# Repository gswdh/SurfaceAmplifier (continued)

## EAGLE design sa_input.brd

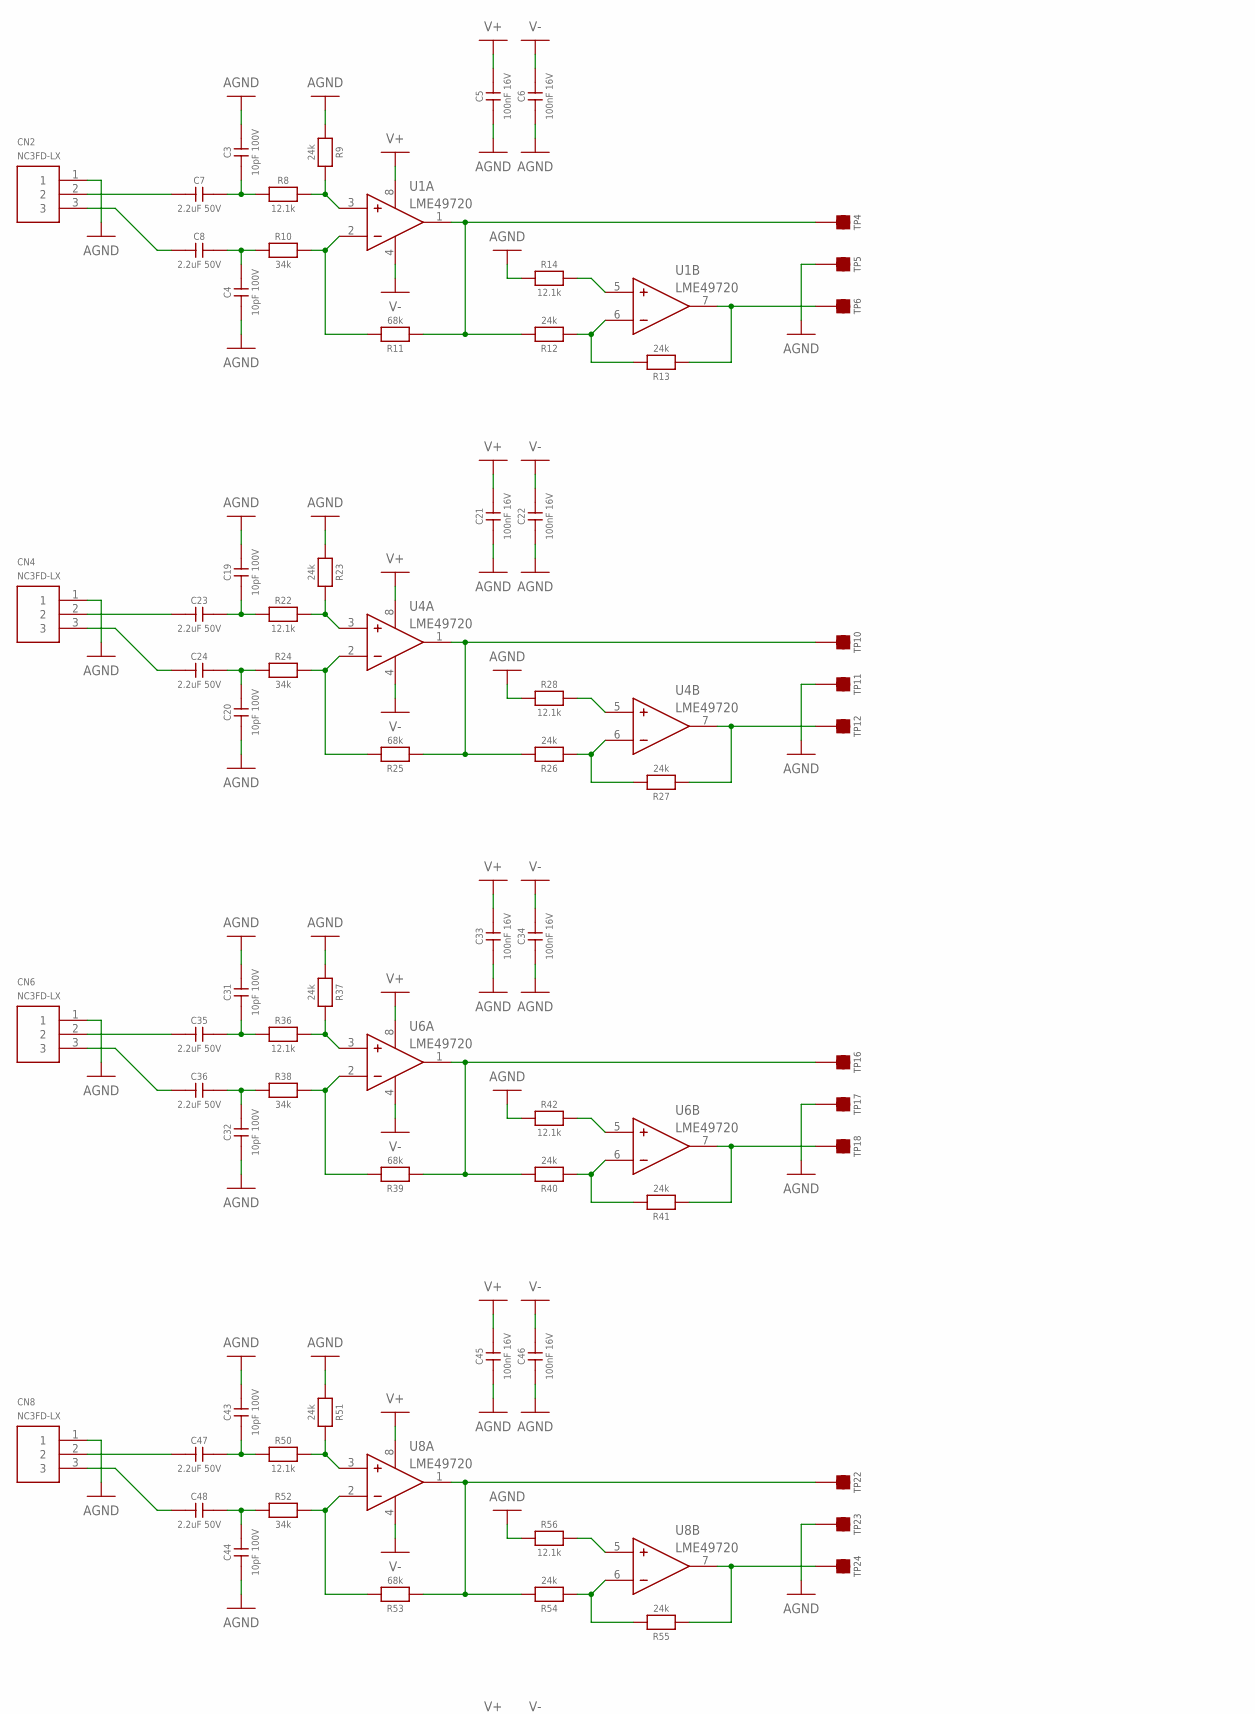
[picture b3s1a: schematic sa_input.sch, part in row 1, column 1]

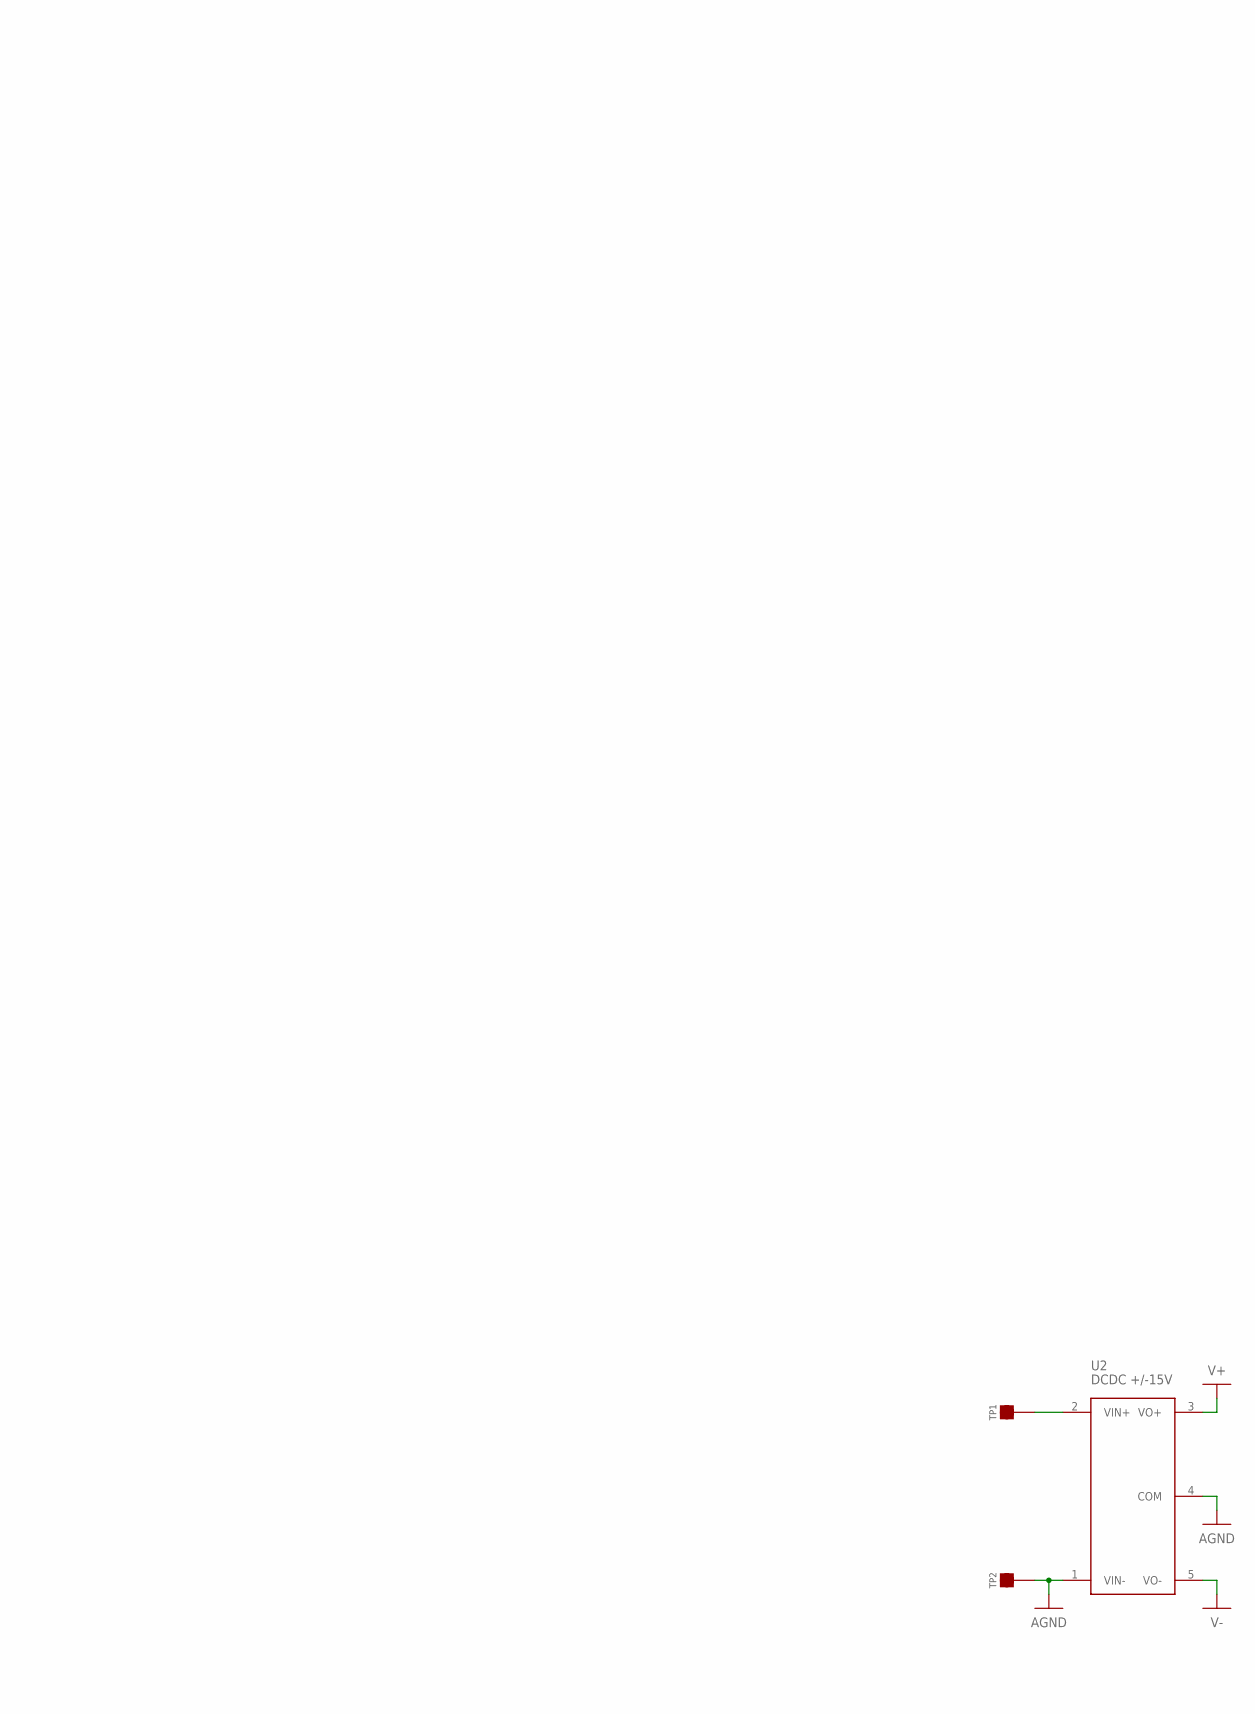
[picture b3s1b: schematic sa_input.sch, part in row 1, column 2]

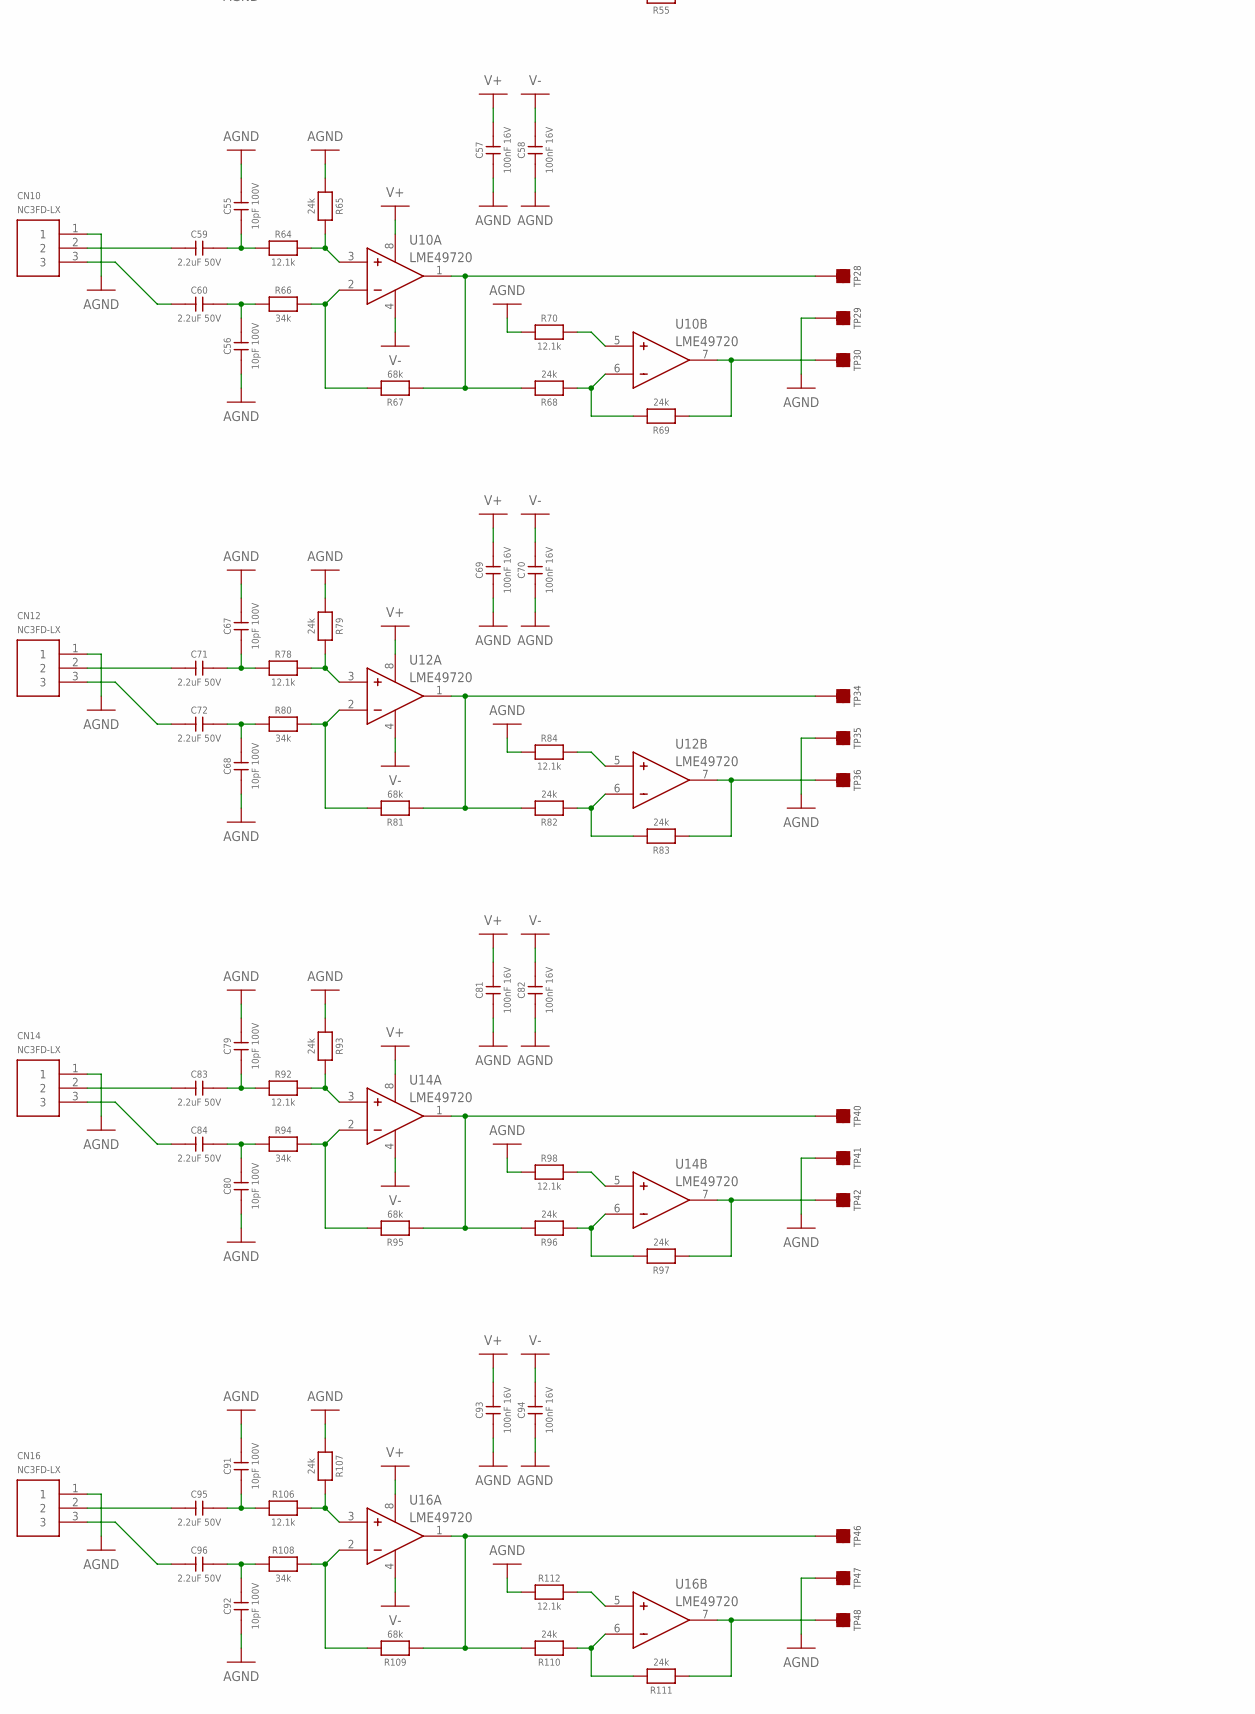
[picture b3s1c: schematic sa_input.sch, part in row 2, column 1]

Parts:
C3, C4, C19, C20, C31, C32, C43, C44, C55, C56, C67, C68, C79, C80, C91, C92: 10pF 100V; 0603
C5, C6, C21, C22, C33, C34, C45, C46, C57, C58, C69, C70, C81, C82, C93, C94: 100nF 16V; 0603
C7, C8, C23, C24, C35, C36, C47, C48, C59, C60, C71, C72, C83, C84, C95, C96: 2.2uF 50V; 5X7.2BOX
CN2, CN4, CN6, CN8, CN10, CN12, CN14, CN16: NC3FD-LX
R8, R14, R22, R28, R36, R42, R50, R56, R64, R70, R78, R84, R92, R98, R106, R112: 12.1k; 0603
R9, R12, R13, R23, R26, R27, R37, R40, R41, R51, R54, R55, R65, R68, R69, R79, R82, R83, R93, R96, R97, R107, R110, R111: 24k; 0603
R10, R24, R38, R52, R66, R80, R94, R108: 34k; 0603
R11, R25, R39, R53, R67, R81, R95, R109: 68k; 0603
TP1, TP2, TP4, TP5, TP6, TP10, TP11, TP12, TP16, TP17, TP18, TP22, TP23, TP24, TP28, TP29, TP30, TP34, TP35, TP36, TP40, TP41, TP42, TP46, TP47, TP48: TEST_POINT_SQUARE; OSPREY_HSS_PAD
U1, U4, U6, U8, U10, U12, U14, U16: LME49720; SO8
U2: DCDC +/-15V; PDQE10

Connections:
AGND: C3.1, C4.1, C5.1, C6.1, C19.1, C20.1, C21.1, C22.1, C31.1, C32.1, C33.1, C34.1, C43.1, C44.1, C45.1, C46.1, C55.1, C56.1, C57.1, C58.1, C67.1, C68.1, C69.1, C70.1, C79.1, C80.1, C81.1, C82.1, C91.1, C92.1, C93.1, C94.1, CN2.1, CN4.1, CN6.1, CN8.1, CN10.1, CN12.1, CN14.1, CN16.1, R9.1, R14.1, R23.1, R28.1, R37.1, R42.1, R51.1, R56.1, R65.1, R70.1, R79.1, R84.1, R93.1, R98.1, R107.1, R112.1, TP2.1, TP5.1, TP11.1, TP17.1, TP23.1, TP29.1, TP35.1, TP41.1, TP47.1, U2.1 (VIN-), U2.4 (COM)
unnamed: TP1.1, U2.2 (VIN+)
unnamed: R8.2, R9.2, U1.3 (+)
unnamed: R10.2, R11.2, U1.2 (-)
unnamed: C3.2, C7.2, R8.1
unnamed: C4.2, C8.2, R10.1
unnamed: C7.1, CN2.2
unnamed: C8.1, CN2.3
unnamed: R12.1, R13.2, U1.6 (-)
unnamed: R14.2, U1.5 (+)
unnamed: R22.2, R23.2, U4.3 (+)
unnamed: R24.2, R25.2, U4.2 (-)
unnamed: C19.2, C23.2, R22.1
unnamed: C20.2, C24.2, R24.1
unnamed: C23.1, CN4.2
unnamed: C24.1, CN4.3
unnamed: R26.1, R27.2, U4.6 (-)
unnamed: R28.2, U4.5 (+)
unnamed: R36.2, R37.2, U6.3 (+)
unnamed: R38.2, R39.2, U6.2 (-)
unnamed: C31.2, C35.2, R36.1
unnamed: C32.2, C36.2, R38.1
unnamed: C35.1, CN6.2
unnamed: C36.1, CN6.3
unnamed: R40.1, R41.2, U6.6 (-)
unnamed: R42.2, U6.5 (+)
unnamed: R50.2, R51.2, U8.3 (+)
unnamed: R52.2, R53.2, U8.2 (-)
unnamed: C43.2, C47.2, R50.1
unnamed: C44.2, C48.2, R52.1
unnamed: C47.1, CN8.2
unnamed: C48.1, CN8.3
unnamed: R54.1, R55.2, U8.6 (-)
unnamed: R56.2, U8.5 (+)
unnamed: R64.2, R65.2, U10.3 (+)
unnamed: R66.2, R67.2, U10.2 (-)
unnamed: C55.2, C59.2, R64.1
unnamed: C56.2, C60.2, R66.1
unnamed: C59.1, CN10.2
unnamed: C60.1, CN10.3
unnamed: R68.1, R69.2, U10.6 (-)
unnamed: R70.2, U10.5 (+)
unnamed: R78.2, R79.2, U12.3 (+)
unnamed: R80.2, R81.2, U12.2 (-)
unnamed: C67.2, C71.2, R78.1
unnamed: C68.2, C72.2, R80.1
unnamed: C71.1, CN12.2
unnamed: C72.1, CN12.3
unnamed: R82.1, R83.2, U12.6 (-)
unnamed: R84.2, U12.5 (+)
unnamed: R92.2, R93.2, U14.3 (+)
unnamed: R94.2, R95.2, U14.2 (-)
unnamed: C79.2, C83.2, R92.1
unnamed: C80.2, C84.2, R94.1
unnamed: C83.1, CN14.2
unnamed: C84.1, CN14.3
unnamed: R96.1, R97.2, U14.6 (-)
unnamed: R98.2, U14.5 (+)
unnamed: R106.2, R107.2, U16.3 (+)
unnamed: R108.2, R109.2, U16.2 (-)
unnamed: C91.2, C95.2, R106.1
unnamed: C92.2, C96.2, R108.1
unnamed: C95.1, CN16.2
unnamed: C96.1, CN16.3
unnamed: R110.1, R111.2, U16.6 (-)
unnamed: R112.2, U16.5 (+)
V+: C5.2, C21.2, C33.2, C45.2, C57.2, C69.2, C81.2, C93.2, U1.8 (V+), U2.3 (VO+), U4.8 (V+), U6.8 (V+), U8.8 (V+), U10.8 (V+), U12.8 (V+), U14.8 (V+), U16.8 (V+)
V-: C6.2, C22.2, C34.2, C46.2, C58.2, C70.2, C82.2, C94.2, U1.4 (V-), U2.5 (VO-), U4.4 (V-), U6.4 (V-), U8.4 (V-), U10.4 (V-), U12.4 (V-), U14.4 (V-), U16.4 (V-)
VOUT_N_1: R13.1, TP6.1, U1.7 (OUT)
VOUT_N_3: R27.1, TP12.1, U4.7 (OUT)
VOUT_N_5: R41.1, TP18.1, U6.7 (OUT)
VOUT_N_7: R55.1, TP24.1, U8.7 (OUT)
VOUT_N_9: R69.1, TP30.1, U10.7 (OUT)
VOUT_N_11: R83.1, TP36.1, U12.7 (OUT)
VOUT_N_13: R97.1, TP42.1, U14.7 (OUT)
VOUT_N_15: R111.1, TP48.1, U16.7 (OUT)
VOUT_P_1: R11.1, R12.2, TP4.1, U1.1 (OUT)
VOUT_P_3: R25.1, R26.2, TP10.1, U4.1 (OUT)
VOUT_P_5: R39.1, R40.2, TP16.1, U6.1 (OUT)
VOUT_P_7: R53.1, R54.2, TP22.1, U8.1 (OUT)
VOUT_P_9: R67.1, R68.2, TP28.1, U10.1 (OUT)
VOUT_P_11: R81.1, R82.2, TP34.1, U12.1 (OUT)
VOUT_P_13: R95.1, R96.2, TP40.1, U14.1 (OUT)
VOUT_P_15: R109.1, R110.2, TP46.1, U16.1 (OUT)

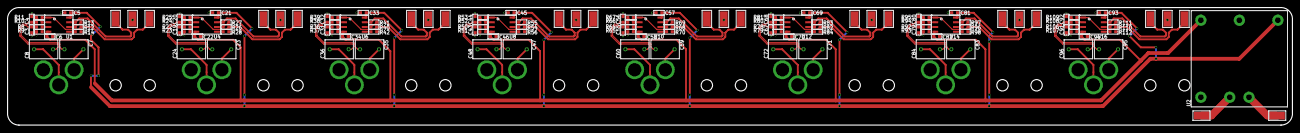
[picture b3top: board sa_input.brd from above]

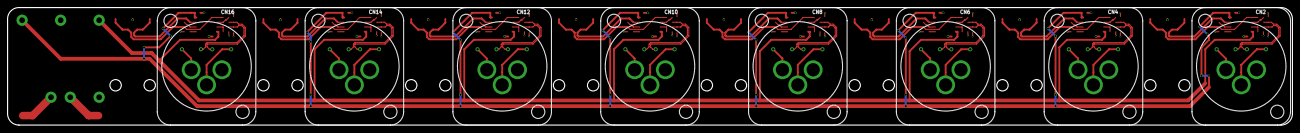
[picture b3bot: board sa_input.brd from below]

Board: 4 copper layers, 339.0 x 31.0 mm, 147 parts (8 on the bottom side), 84 nets.

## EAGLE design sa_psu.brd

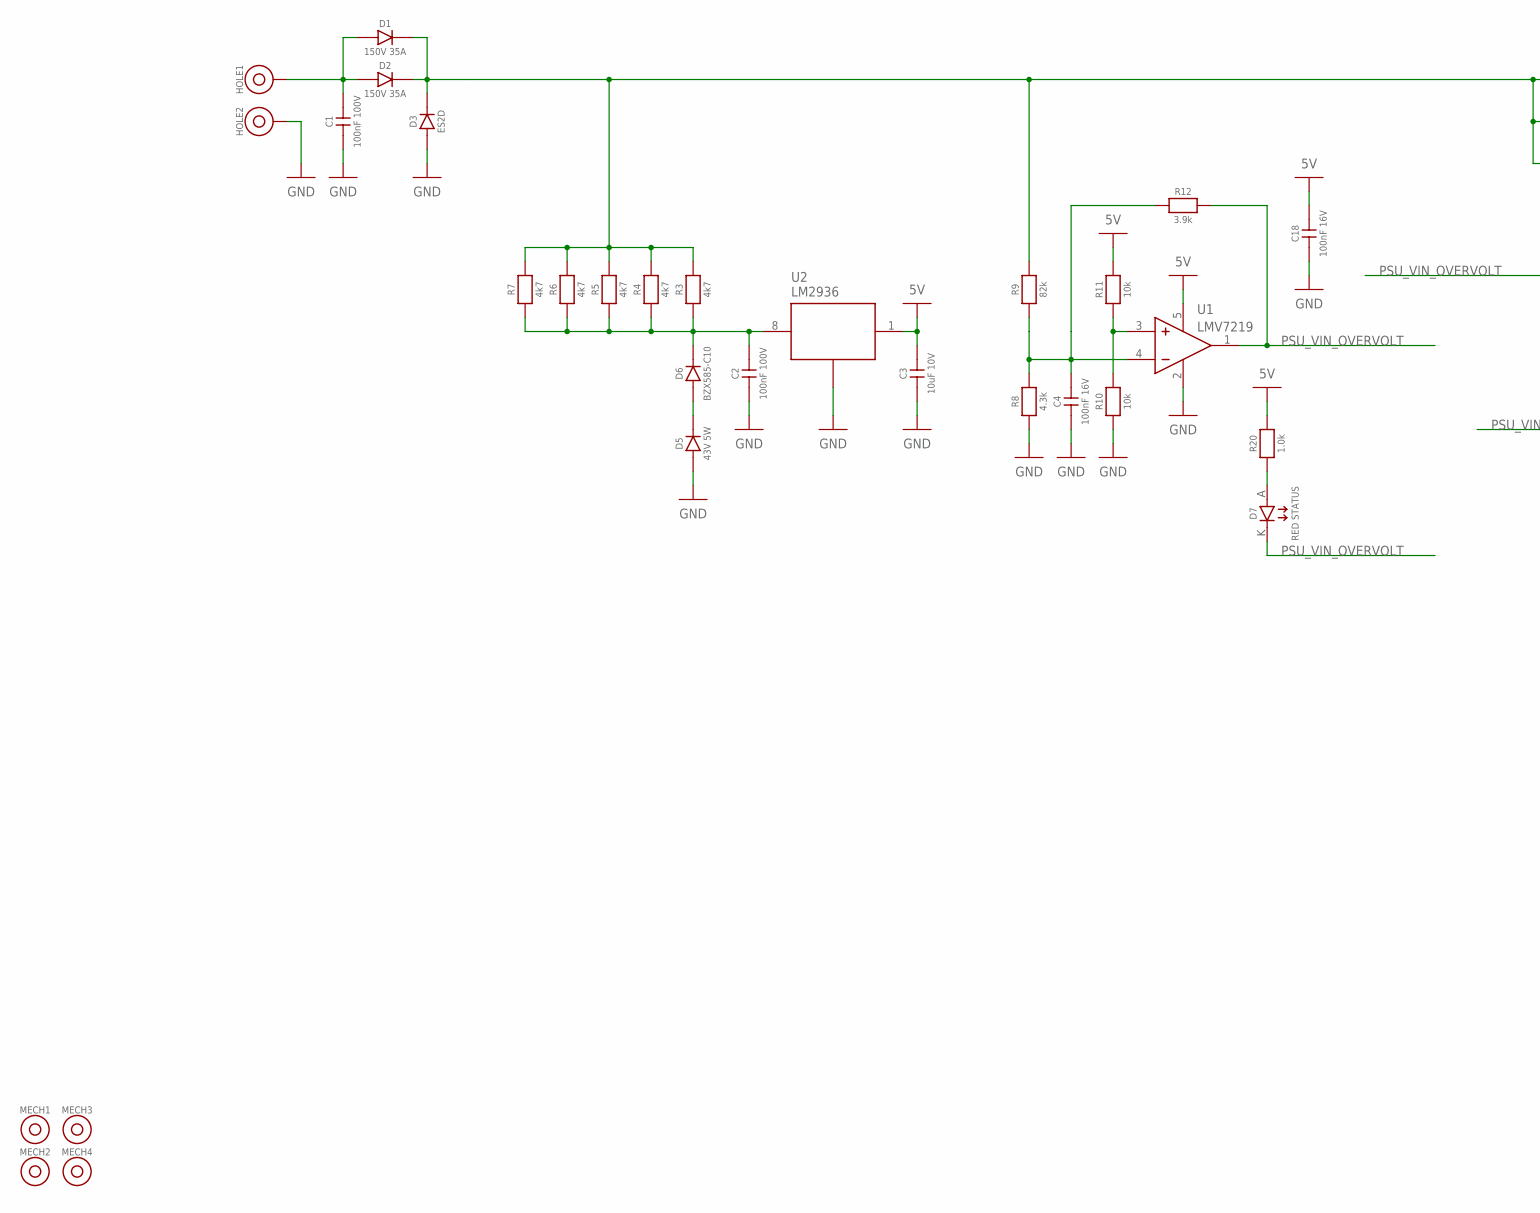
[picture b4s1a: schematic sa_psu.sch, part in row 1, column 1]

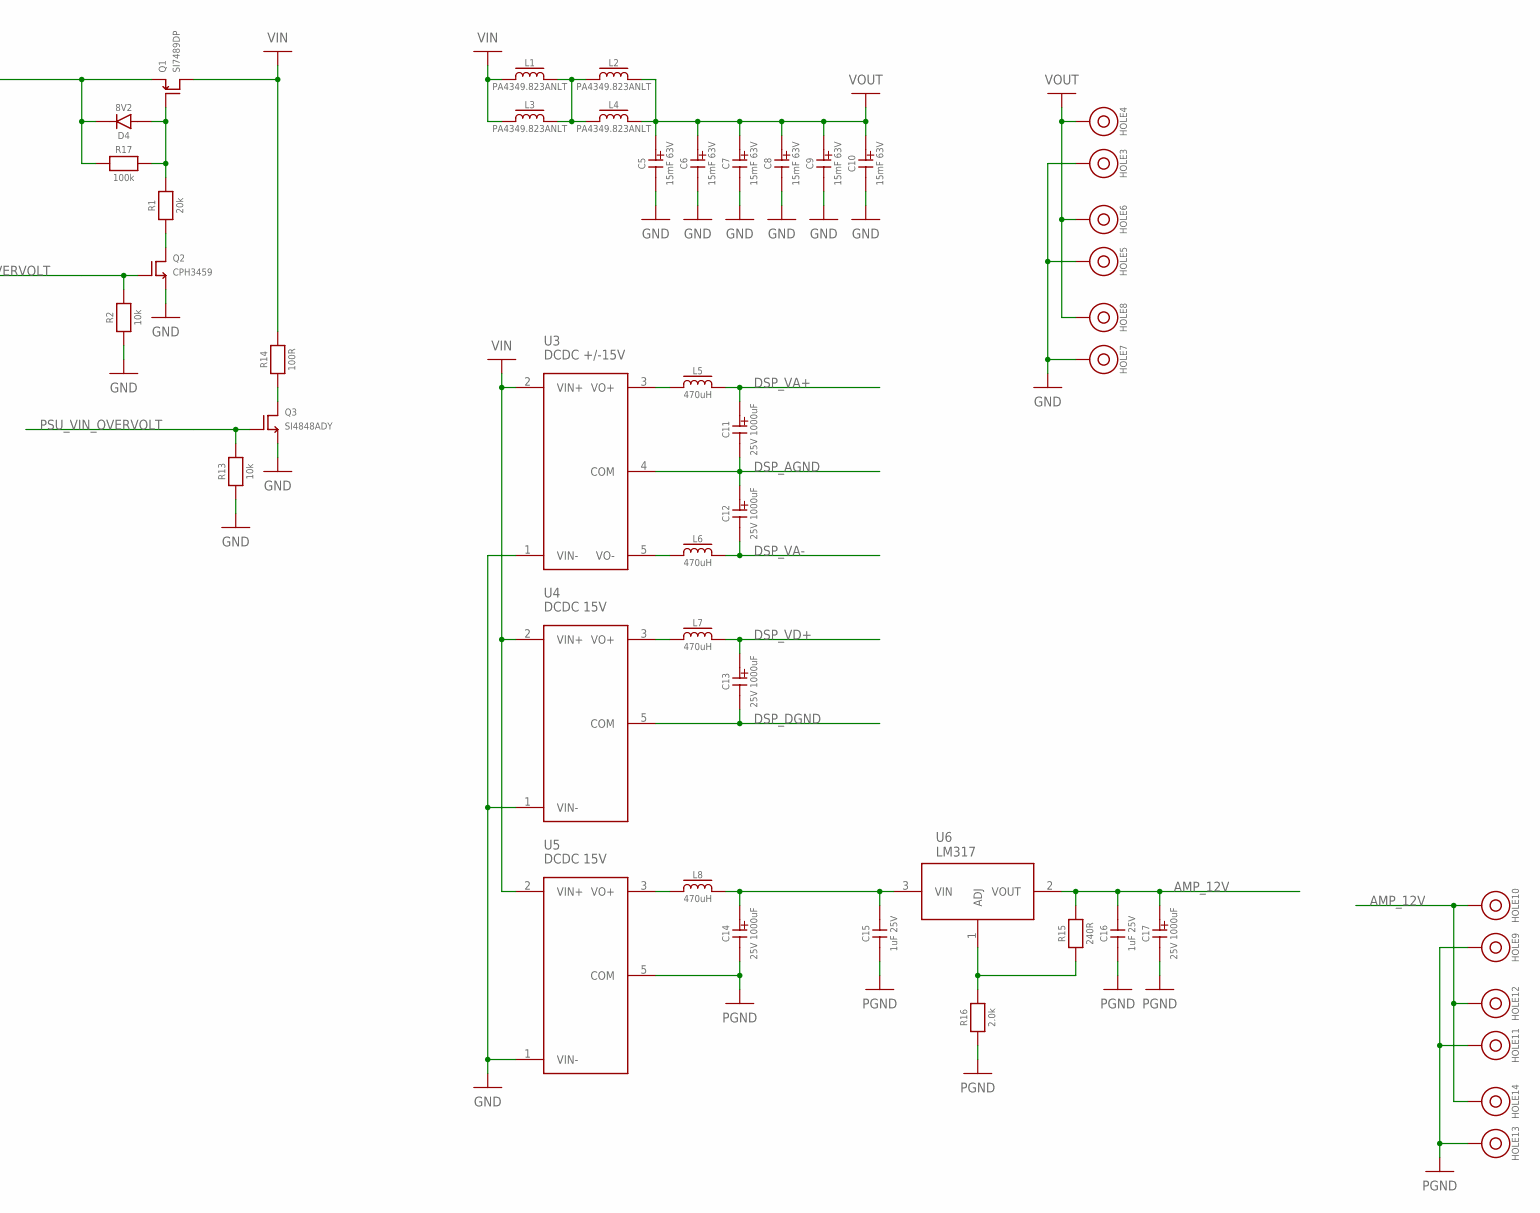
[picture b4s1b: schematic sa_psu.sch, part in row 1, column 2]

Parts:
C1, C2: 100nF 100V; 0603
C3: 10uF 10V; 0603
C4, C18: 100nF 16V; 0603
C5, C6, C7, C8, C9, C10: 15mF 63V; 35MM/10MMCAP
C11, C12, C13, C14, C17: 25V 1000uF; 10MM_RADIAL_5MM_PITCH
C15, C16: 1uF 25V; 0603
D1, D2: 150V 35A; TO252
D3: ES2D; DO214AA
D4: 8V2; SOD80
D5: 43V 5W; 017AA-01
D6: BZX585-C10; SOD_523
D7: RED STATUS; VLMT3100
HOLE1, HOLE2, HOLE3, HOLE4, HOLE5, HOLE6, HOLE7, HOLE8: 4mm ID; MOUNTHOLE_8X4
HOLE9, HOLE10, HOLE11, HOLE12, HOLE13, HOLE14: MOUNTHOLE_METAL4X2; 4X2
L1, L2, L3, L4: PA4349.823ANLT; PA4349.ZZZANLT
L5, L6, L7, L8: 470uH; SRN1060
MECH1, MECH2, MECH3, MECH4: 6mm x 3mm; MOUNTHOLE_6X3
Q1: SI7489DP; SO8_POWERPAK
Q2: CPH3459; SOT23-3
Q3: SI4848ADY; SO8
R1: 20k; 0603
R2, R10, R11, R13: 10k; 0603
R3, R4, R5, R6, R7: 4k7; 1206
R8: 4.3k; 0603
R9: 82k; 0603
R12: 3.9k; 0603
R14: 100R; 15MM_TH
R15: 240R; 0603
R16: 2.0k; 0603
R17: 100k; 0603
R20: 1.0k; 0603
U1: LMV7219; SOT23-5
U2: LM2936; SO8
U3: DCDC +/-15V; PDQE10
U4, U5: DCDC 15V; PDQE10
U6: LM317; TO220

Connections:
5V: C3.2, C18.2, R11.2, R20.2, U1.5 (VCC), U2.1 (VOUT)
AMP_12V: C16.2, C17.2 (A), HOLE10.1, HOLE12.1, HOLE14.1, R15.2, U6.2 (VOUT)
DSP_AGND: C11.1 (K), C12.2 (A), U3.4 (COM)
DSP_DGND: C13.1 (K), U4.5 (COM)
DSP_VA+: C11.2 (A), L5.2
DSP_VA-: C12.1 (K), L6.2
DSP_VD+: C13.2 (A), L7.2
GND: C1.1, C2.1, C3.1, C4.1, C5.P$2 (2), C6.P$2 (2), C7.P$2 (2), C8.P$2 (2), C9.P$2 (2), C10.P$2 (2), C18.1, D3.A, D5.A, HOLE2.1, HOLE3.1, HOLE5.1, HOLE7.1, Q2.3 (S), Q3.1 (S), Q3.2 (S), Q3.3 (S), R2.1, R8.1, R10.1, R13.1, U1.2 (GND), U2.2 (GND), U2.3 (GND), U2.6 (GND), U2.7 (GND), U3.1 (VIN-), U4.1 (VIN-), U5.1 (VIN-)
unnamed: C1.2, D1.1 (A), D1.3 (A), D2.1 (A), D2.3 (A), HOLE1.1
unnamed: C4.2, R8.2, R9.1, R12.1, U1.4 (-)
unnamed: D4.A, Q1.4 (G), R1.2, R17.2
unnamed: L1.2, L2.1, L3.2, L4.1
unnamed: Q2.2 (D), R1.1
unnamed: D5.K, D6.A
unnamed: C2.2, D6.K, R3.1, R4.1, R5.1, R6.1, R7.1, U2.8 (VIN)
unnamed: D1.4 (K), D2.4 (K), D3.K, D4.K, Q1.1 (S), Q1.2 (S), Q1.3 (S), R3.2, R4.2, R5.2, R6.2, R7.2, R9.2, R17.1
unnamed: R10.2, R11.1, U1.3 (+)
unnamed: D7.A, R20.1
unnamed: L5.1, U3.3 (VO+)
unnamed: L6.1, U3.5 (VO-)
unnamed: R15.1, R16.2, U6.1 (ADJ)
unnamed: C14.2 (A), C15.2, L8.2, U6.3 (VIN)
unnamed: L8.1, U5.3 (VO+)
unnamed: L7.1, U4.3 (VO+)
unnamed: Q3.5 (D), Q3.6 (D), Q3.7 (D), Q3.8 (D), R14.1
PGND: C14.1 (K), C15.1, C16.1, C17.1 (K), HOLE9.1, HOLE11.1, HOLE13.1, R16.1, U5.5 (COM)
PSU_VIN_OVERVOLT: D7.K, Q2.1 (G), Q3.4 (G), R2.2, R12.2, R13.2, U1.1 (VOUT)
VIN: L1.1, L3.1, Q1.5 (D), Q1.6 (D), Q1.7 (D), Q1.8 (D), Q1.PAD (D), R14.2, U3.2 (VIN+), U4.2 (VIN+), U5.2 (VIN+)
VOUT: C5.P$1 (1), C6.P$1 (1), C7.P$1 (1), C8.P$1 (1), C9.P$1 (1), C10.P$1 (1), HOLE4.1, HOLE6.1, HOLE8.1, L2.2, L4.2

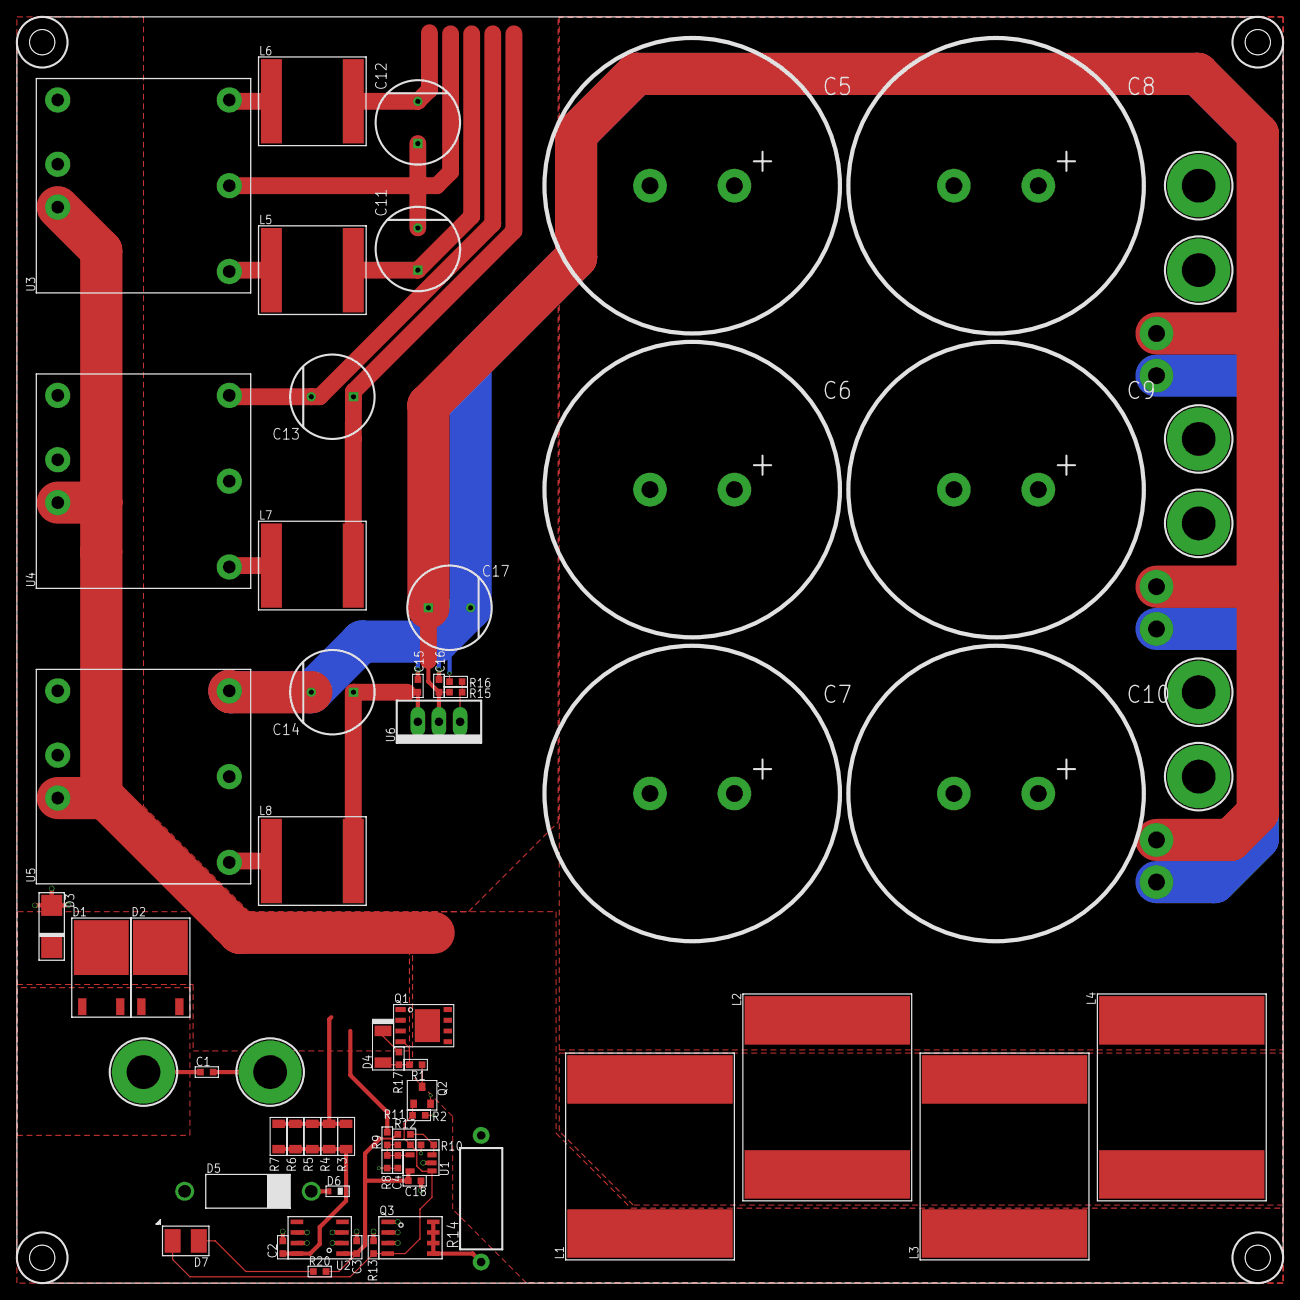
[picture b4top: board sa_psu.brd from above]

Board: 2 copper layers, 150.0 x 150.0 mm, 78 parts (0 on the bottom side), 29 nets.

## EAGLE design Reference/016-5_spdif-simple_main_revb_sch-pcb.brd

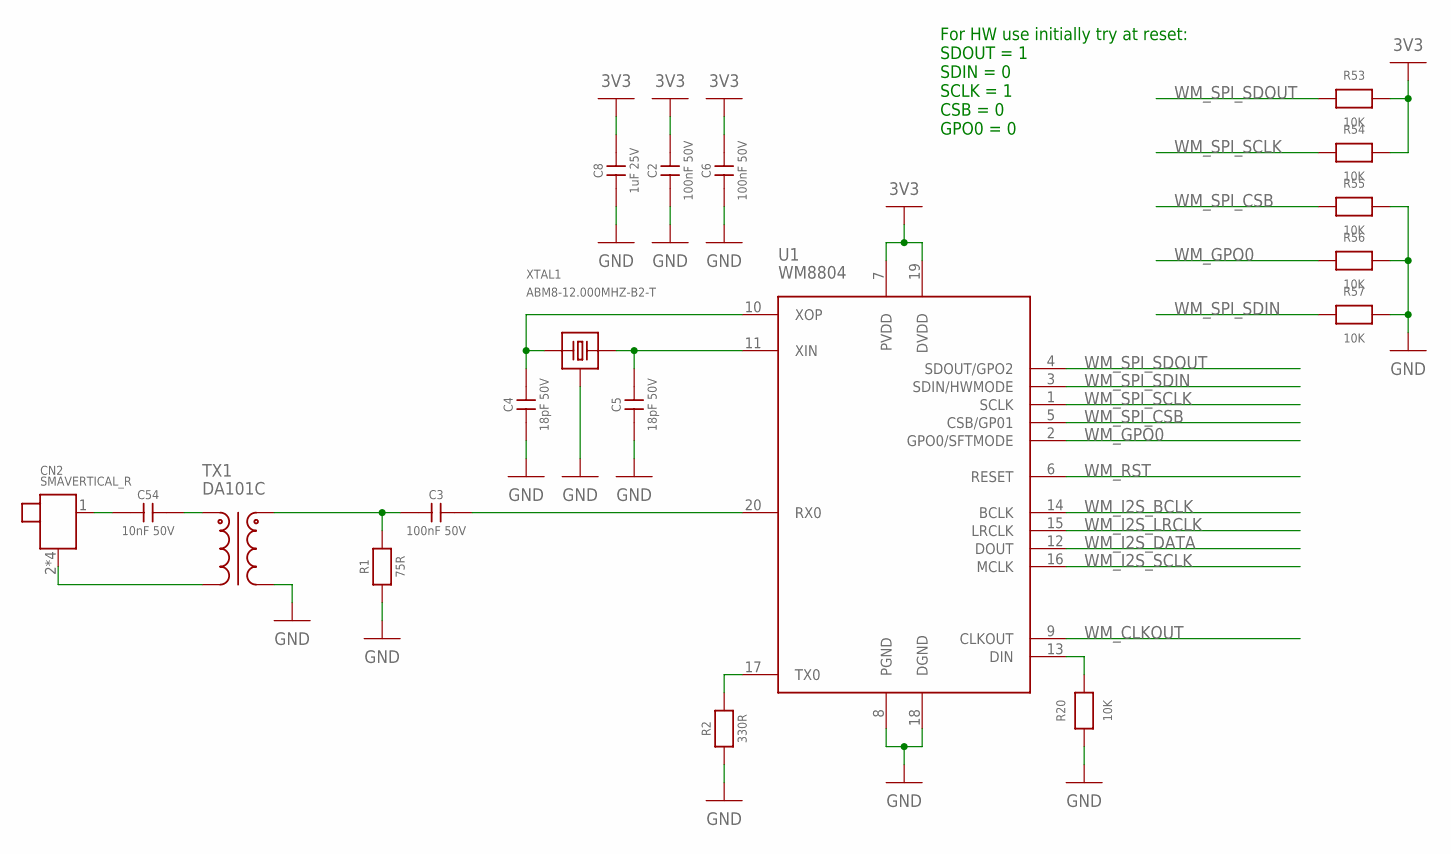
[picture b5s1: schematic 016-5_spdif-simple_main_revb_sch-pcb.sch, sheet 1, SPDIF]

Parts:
C2, C3: 100nF 50V; 0603
C4, C5: 18pF 50V; 0603
C6: 100nF 50V; 0603; FARNELL 2407338
C8: 1uF 25V; 0603
C54: 10nF 50V; 0603
CN2: SMAVERTICAL_R; SMAVERTICAL
R1: 75R; 0603
R2: 330R; 0603
R20: 10K; 0603; FARNELL 1469748
R53, R54, R55, R56, R57: 10K; 0603
TX1: DA101C; DA10XC
U1: WM8804; SSOP20-5MM
XTAL1: ABM8-12.000MHZ-B2-T; 3.2X3.5SMD

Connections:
3V3: C2.2, C6.2, C8.2, R53.2, R54.2, U1.7 (PVDD), U1.19 (DVDD); also elsewhere on the board
GND: C2.1, C4.1, C5.1, C6.1, C8.1, R1.1, R2.1, R20.1, R55.2, R56.2, R57.2, TX1.4 (B2), U1.8 (PGND), U1.18 (DGND), XTAL1.2 (GND), XTAL1.4 (GND); also elsewhere on the board
unnamed: C3.2, U1.20 (RX0)
unnamed: R2.2, U1.17 (TX0)
unnamed: C4.2, U1.10 (XOP), XTAL1.3
unnamed: C5.2, U1.11 (XIN), XTAL1.1
unnamed: R20.2, U1.13 (DIN)
unnamed: C54.2, TX1.1 (A1)
unnamed: CN2.2 (5), CN2.3 (5), CN2.4 (5), CN2.5, TX1.3 (A2)
unnamed: C54.1, CN2.1
SPDIF_IN: C3.1, R1.2, TX1.6 (B1)
WM_CLKOUT: U1.9 (CLKOUT); also elsewhere on the board
WM_GPO0: R56.1, U1.2 (GPO0/SFTMODE); also elsewhere on the board
WM_I2S_BCLK: U1.14 (BCLK); also elsewhere on the board
WM_I2S_DATA: U1.12 (DOUT); also elsewhere on the board
WM_I2S_LRCLK: U1.15 (LRCLK); also elsewhere on the board
WM_I2S_SCLK: U1.16 (MCLK); also elsewhere on the board
WM_RST: U1.6 (RESET); also elsewhere on the board
WM_SPI_CSB: R55.1, U1.5 (CSB/GP01); also elsewhere on the board
WM_SPI_SCLK: R54.1, U1.1 (SCLK); also elsewhere on the board
WM_SPI_SDIN: R57.1, U1.3 (SDIN/HWMODE); also elsewhere on the board
WM_SPI_SDOUT: R53.1, U1.4 (SDOUT/GPO2); also elsewhere on the board

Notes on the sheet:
For HW use initially try at reset: SDOUT = 1 SDIN = 0 SCLK = 1 CSB = 0 GPO0 = 0
